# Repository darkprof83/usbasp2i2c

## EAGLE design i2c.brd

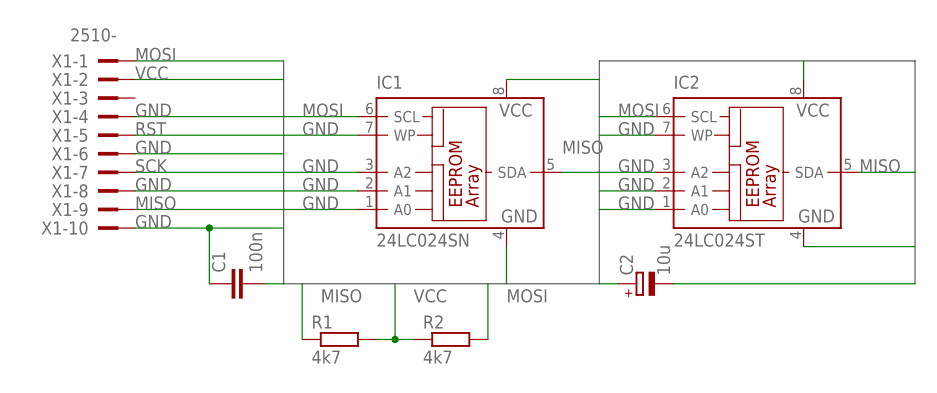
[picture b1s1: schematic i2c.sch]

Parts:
C1: 100n; C0805K
C2: 10u; SMC_D
IC1: 24LC024SN; SO-08
IC2: 24LC024ST; TSSOP8
R1, R2: 4k7; 0204/7
X1: 2510-; PAK100/2500-10

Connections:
GND: C1.1, C2.-, IC1.1 (A0), IC1.2 (A1), IC1.3 (A2), IC1.4 (GND), IC1.7 (WP), IC2.1 (A0), IC2.2 (A1), IC2.3 (A2), IC2.4 (GND), IC2.7 (WP), X1.4, X1.6, X1.8, X1.10
MISO: IC1.5 (SDA), IC2.5 (SDA), R1.1, X1.9
MOSI: IC1.6 (SCL), IC2.6 (SCL), R2.2, X1.1
RST: X1.5
SCK: X1.7
VCC: C1.2, C2.+, IC1.8 (VCC), IC2.8 (VCC), R1.2, R2.1, X1.2

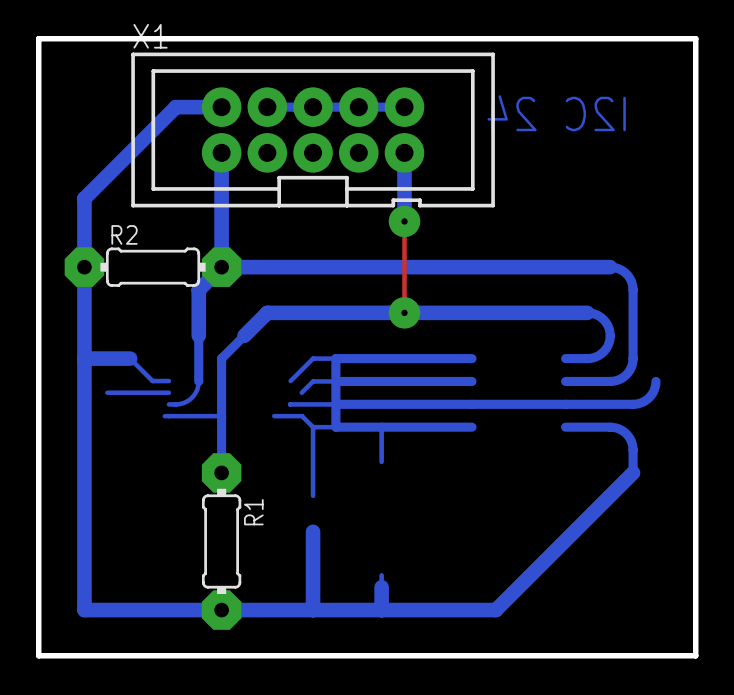
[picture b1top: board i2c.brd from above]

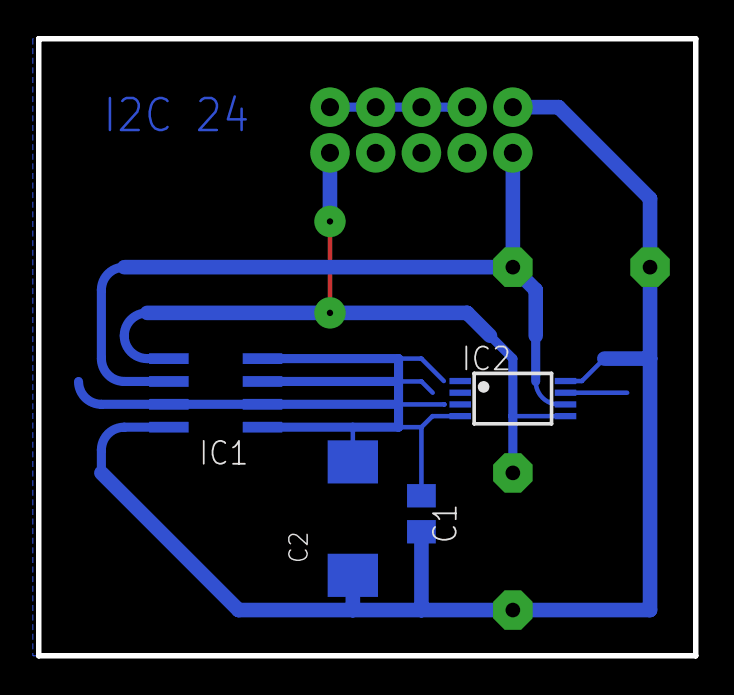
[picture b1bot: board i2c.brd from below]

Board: 2 copper layers, 36.5 x 34.3 mm, 7 parts (4 on the bottom side), 4 nets.

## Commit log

2020-05-07 Черновой вариант платы
2020-05-08 Добавлены технологические правила
2020-05-08 Черновой вариант с заливкой
2020-05-08 Изменены диаметры всех отверстий на 0.3мм
2020-05-08 pdf файлы игнорируются
2020-05-08 Подправлена заливка
2020-05-08 Добавлена надпись
2020-05-08 Добавлены метки первого вывода
2020-05-08 Подправлены дорожки
2020-05-08 Увеличено расстояние до заливки
2020-10-05 Увеличина ширина контура платы
